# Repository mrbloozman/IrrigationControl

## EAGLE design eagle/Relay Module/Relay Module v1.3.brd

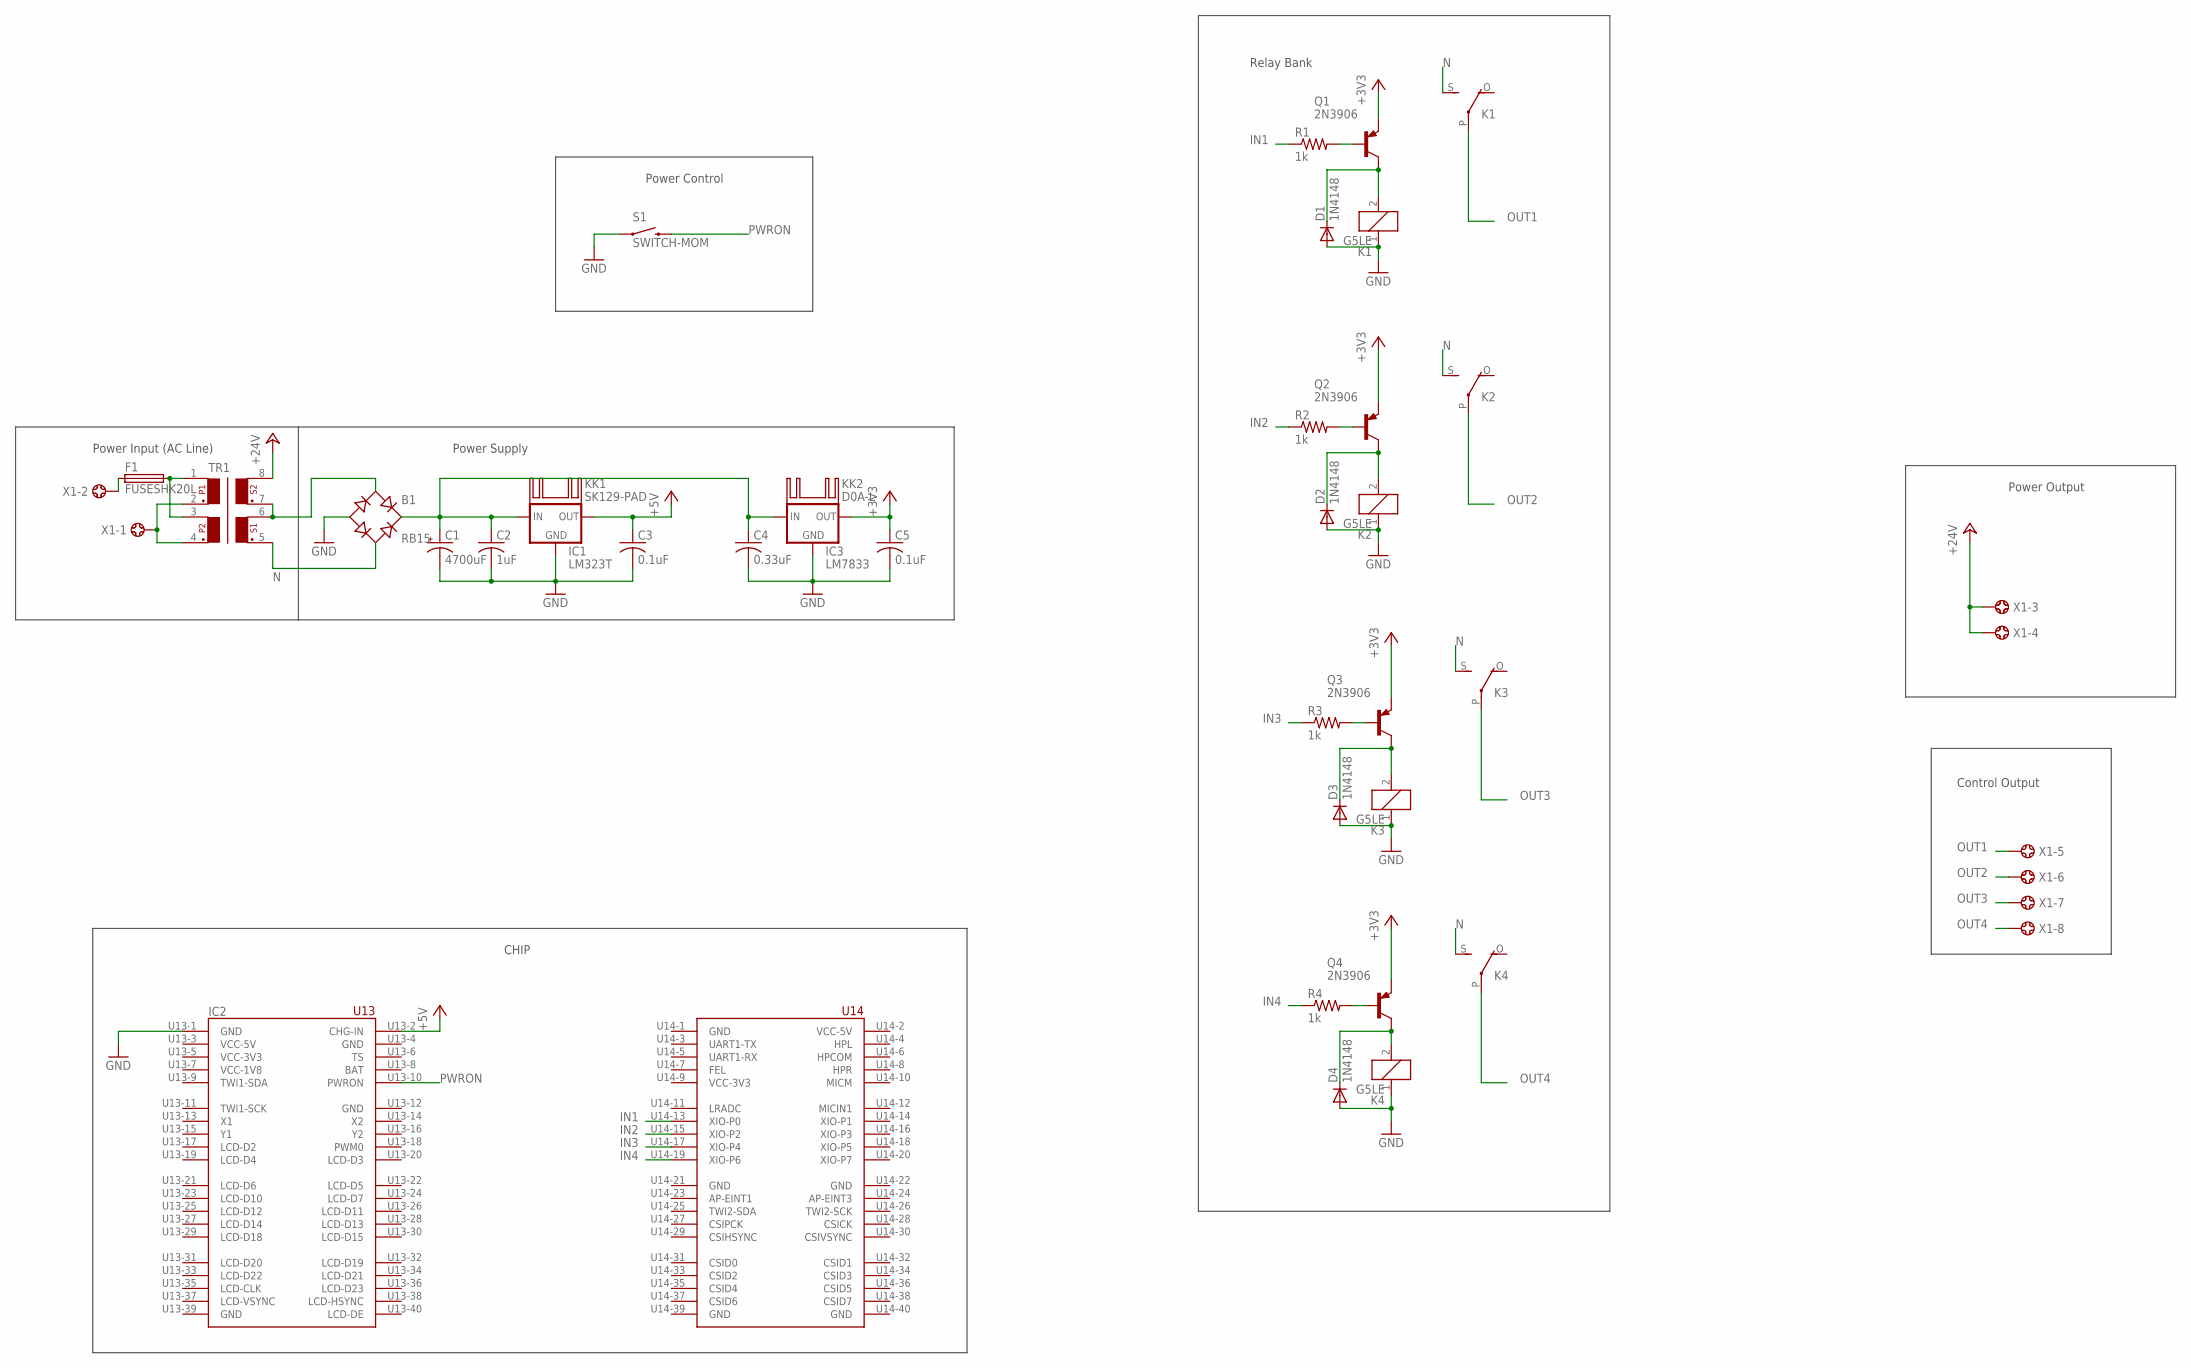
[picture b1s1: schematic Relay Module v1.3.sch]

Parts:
B1: RB15
C1: 4700uF; E7,5-18
C2: 1uF; C025-025X050
C3, C5: 0.1uF; C025-025X050
C4: 0.33uF; C025-025X050
D1, D2, D3, D4: 1N4148; DO35-7
F1: FUSESHK20L; SHK20L
IC1: LM323T; TO220S
IC2: C_H_I_P-1_0
IC3: LM7833; 78XXL
K1, K2, K3, K4: G5LE
KK1: SK129-PAD; SK129
KK2: D0A-L; D02A-L
Q1, Q2, Q3, Q4: 2N3906; TO92
R1, R2, R3, R4: 1k; 0207/10
S1: SWITCH-MOM; TACTILE-PTH
TR1: FS24-1500-C2
X1: 5202-08-N-02

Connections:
+3V3: C5.1, IC3.OUT, Q1.3 (E), Q2.3 (E), Q3.3 (E), Q4.3 (E)
+5V: C3.1, IC1.3 (OUT), IC2.U13-2 (CHG-IN)
+24V: TR1.8, X1.3, X1.4
BAT: IC2.U13-8 (BAT)
GND: B1.-, C1.-, C2.2, C3.2, C4.2, C5.2, D1.A, D2.A, D3.A, D4.A, IC1.2 (GND), IC2.U13-1 (GND), IC2.U13-4 (GND), IC2.U13-12 (GND), IC2.U13-39 (GND), IC2.U14-1 (GND), IC2.U14-21 (GND), IC2.U14-22 (GND), IC2.U14-39 (GND), IC2.U14-40 (GND), IC3.GND, K1.1, K2.1, K3.1, K4.1, S1.1
IN1: IC2.U14-13 (XIO-P0), R1.1
IN2: IC2.U14-15 (XIO-P2), R2.1
IN3: IC2.U14-17 (XIO-P4), R3.1
IN4: IC2.U14-19 (XIO-P6), R4.1
N: B1.AC2, K1.S, K2.S, K3.S, K4.S, TR1.5
unnamed: B1.+, C1.+, C2.1, C4.1, IC1.1 (IN), IC3.IN
unnamed: Q1.2 (B), R1.2
unnamed: F1.2A (2), TR1.1, TR1.3
unnamed: D1.C, K1.2, Q1.1 (C)
unnamed: F1.1A (1), X1.2
unnamed: B1.AC1, TR1.6, TR1.7
unnamed: TR1.2, TR1.4, X1.1
unnamed: D2.C, K2.2, Q2.1 (C)
unnamed: D3.C, K3.2, Q3.1 (C)
unnamed: D4.C, K4.2, Q4.1 (C)
unnamed: Q2.2 (B), R2.2
unnamed: Q3.2 (B), R3.2
unnamed: Q4.2 (B), R4.2
OUT1: K1.P, X1.5
OUT2: K2.P, X1.6
OUT3: K3.P, X1.7
OUT4: K4.P, X1.8
PWRON: IC2.U13-10 (PWRON), S1.3 (2)

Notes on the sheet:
Power Output
Power Supply
Power Input (AC Line)
Relay Bank
Control Output
Power Control
CHIP

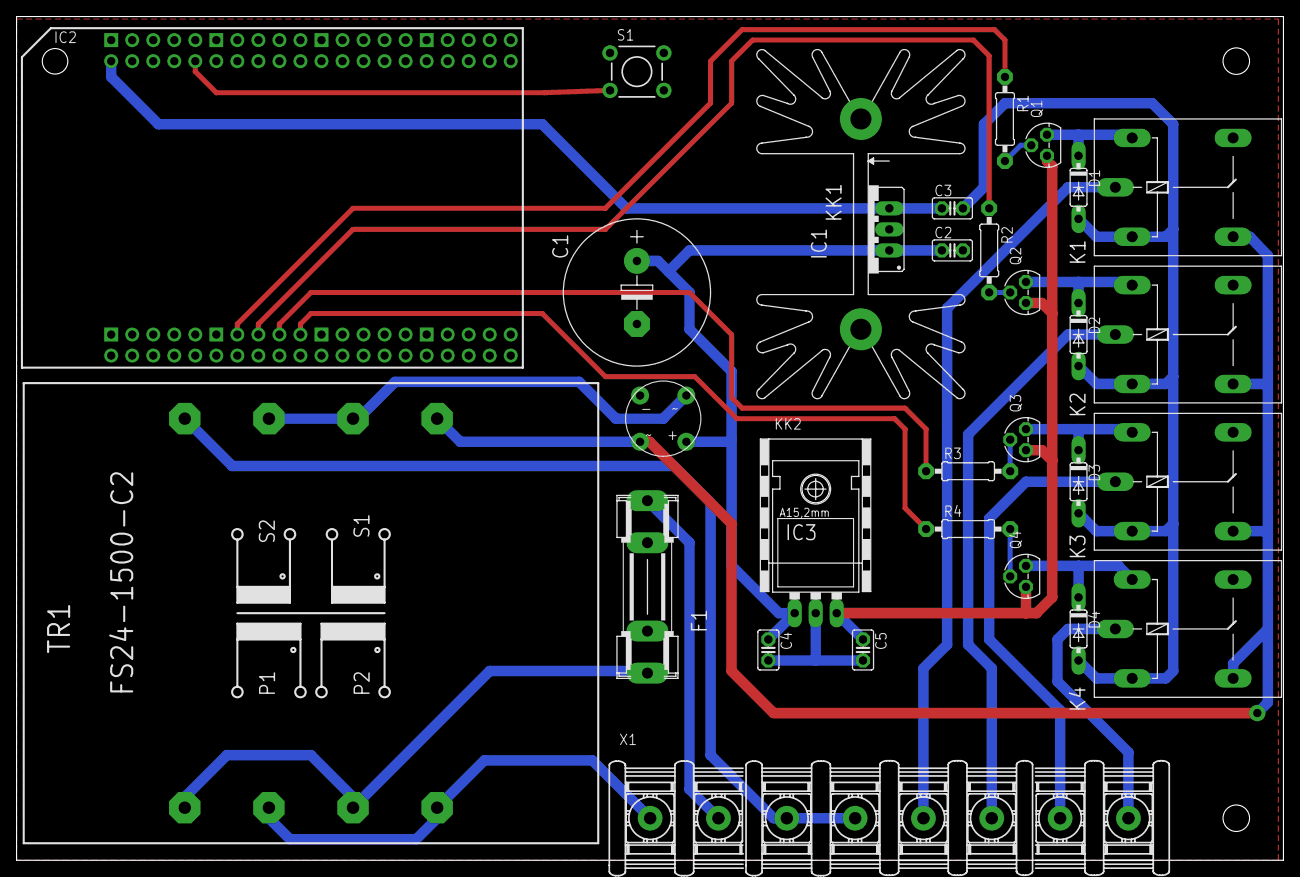
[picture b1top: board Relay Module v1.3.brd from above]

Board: 2 copper layers, 153.0 x 101.9 mm, 31 parts (0 on the bottom side), 27 nets.

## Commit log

2017-04-03 schedules.jade adding edit form
2017-04-04 editSchedule updates to schedules.jade, functions.py, and webservRunTime.py
2017-04-05 Adding docs and eagle files to repository
2017-04-05 UI updates to schedule forms
2017-04-05 UI updates and editSchedule fix
2017-04-25 functions.py - dateOfNextWeekday and getZones
2017-04-25 functions.py getEvents ORDER BY
2017-04-25 functions.py dateOfNextWeekday
2017-04-25 functions.py remove debug printing
2017-04-26 Log paging
2017-04-27 Paging size functionality
2017-04-28 jade template updates
2018-03-31 enabled gpio and scripts folder
2019-07-29 changing to wiringpi for rpi migration
2019-07-29 rpi pins
2019-07-29 cast pins to int
2019-07-29 print debugs
2019-07-29 str casts
2019-07-29 tSchedule zone change to text
2019-07-29 turn off debug printing

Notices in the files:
parts and their libraries:
SparkFun-Electromechanical: Licensing: Creative Commons ShareAlike 4.0 International - https://creativecommons.org/licenses/by-sa/4.0
